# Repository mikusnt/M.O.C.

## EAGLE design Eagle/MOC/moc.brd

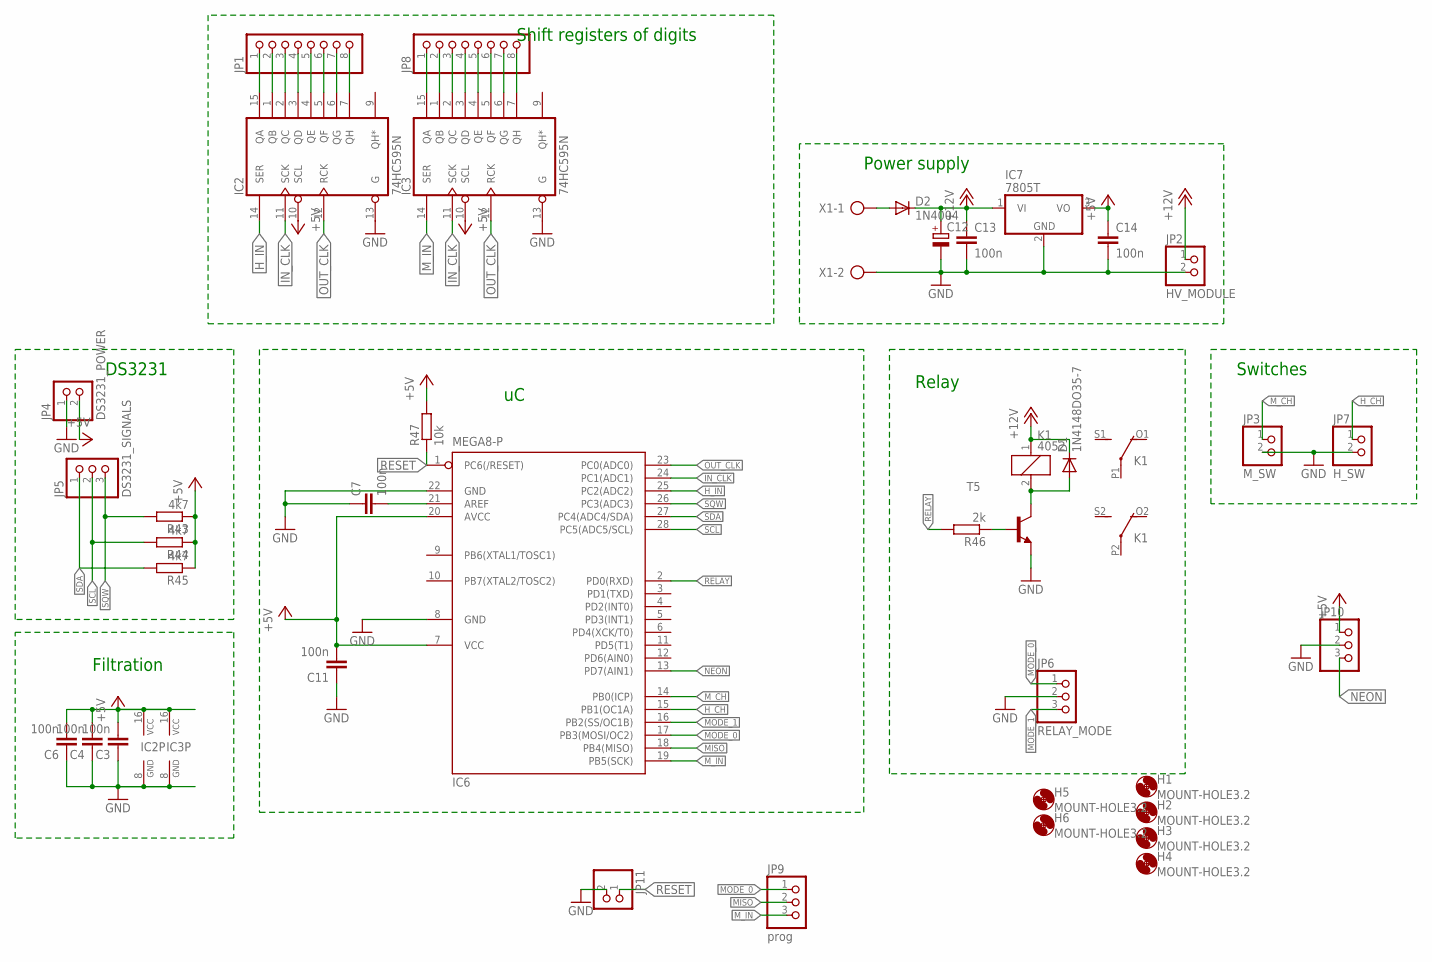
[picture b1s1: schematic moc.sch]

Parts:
C3, C4, C6, C7, C11, C13, C14: 100n; C025-025X050
C12: CPOL-EUE3.5-8; E3,5-8
D1: 1N4148DO35-7; DO35-7
D2: 1N4004; DO41-10
H1, H2, H3, H4, H5, H6: MOUNT-HOLE3.2; 3,2
IC2, IC3: 74HC595N; DIL16
IC6: MEGA8-P; DIL28-3
IC7: 7805T; TO220H
JP1, JP8: PINHD-1X8; 1X08
JP2: HV_MODULE; 1X02
JP3: M_SW; 1X02
JP4: DS3231_POWER; 1X02
JP5: DS3231_SIGNALS; 1X03
JP6: RELAY_MODE; 1X03
JP7: H_SW; 1X02
JP9: prog; 1X03
JP10: PINHD-1X3; 1X03
JP11: PINHD-1X2/90; 1X02/90
K1: 4052; F4052
R43, R44, R45: 4k7; 0207/10
R46: 2k; 0207/7
R47: 10k; 0207/10
T5: BC337-16-NPN-TO92-CBE; TO92-CBE
X1: AK300/2

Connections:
+5V: C3.2, C4.2, C6.2, C11.2, C14.1, IC2.10 (SCL), IC2.16 (VCC), IC3.10 (SCL), IC3.16 (VCC), IC6.7 (VCC), IC6.20 (AVCC), IC7.3 (VO), JP4.2, JP10.1, R43.1, R44.1, R45.1, R47.2
+12V: C12.+, C13.1, D1.C, D2.C, IC7.1 (VI), JP2.1, K1.1
D8: IC3.7 (QH), JP8.8
D9: IC3.6 (QG), JP8.7
D10: IC3.5 (QF), JP8.6
D11: IC3.4 (QE), JP8.5
D12: IC3.3 (QD), JP8.4
D13: IC3.2 (QC), JP8.3
D14: IC3.1 (QB), JP8.2
D15: IC3.15 (QA), JP8.1
D16: IC2.7 (QH), JP1.8
D17: IC2.6 (QG), JP1.7
D18: IC2.5 (QF), JP1.6
D19: IC2.4 (QE), JP1.5
D20: IC2.3 (QD), JP1.4
D21: IC2.2 (QC), JP1.3
D22: IC2.1 (QB), JP1.2
D23: IC2.15 (QA), JP1.1
GND: C3.1, C4.1, C6.1, C7.1, C11.1, C12.-, C13.2, C14.2, IC2.8 (GND), IC2.13 (G), IC3.8 (GND), IC3.13 (G), IC6.8 (GND), IC6.22 (GND), IC7.2 (GND), JP2.2, JP3.2, JP4.1, JP6.2, JP7.2, JP10.2, JP11.2, T5.E, X1.2
H_CH: IC6.15 (PB1(OC1A)), JP7.1
H_IN: IC2.14 (SER), IC6.25 (PC2(ADC2))
IN_CLK: IC2.11 (SCK), IC3.11 (SCK), IC6.24 (PC1(ADC1))
MISO: IC6.18 (PB4(MISO)), JP9.2
MODE_0: IC6.17 (PB3(MOSI/OC2)), JP6.1, JP9.1
MODE_1: IC6.16 (PB2(SS/OC1B)), JP6.3
M_CH: IC6.14 (PB0(ICP)), JP3.1
M_IN: IC3.14 (SER), IC6.19 (PB5(SCK)), JP9.3
unnamed: D2.A, X1.1
unnamed: C7.2, IC6.21 (AREF)
unnamed: D1.A, K1.2, T5.C
unnamed: R46.1, T5.B
NEON: IC6.13 (PD7(AIN1)), JP10.3
OUT_CLK: IC2.12 (RCK), IC3.12 (RCK), IC6.23 (PC0(ADC0))
RELAY: IC6.2 (PD0(RXD)), R46.2
RESET: IC6.1 (PC6(/RESET)), JP11.1, R47.1
SCL: IC6.28 (PC5(ADC5/SCL)), JP5.2, R44.2
SDA: IC6.27 (PC4(ADC4/SDA)), JP5.1, R45.2
SQW: IC6.26 (PC3(ADC3)), JP5.3, R43.2

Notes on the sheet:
DS3231
Relay
Power supply
Filtration
Shift registers of digits
Switches

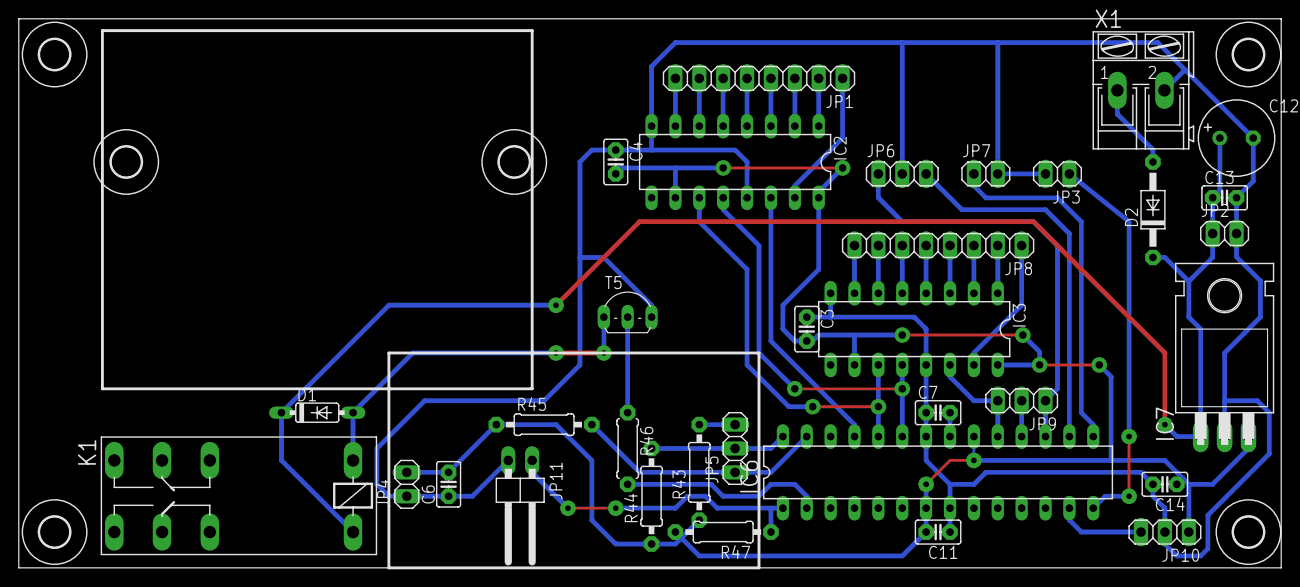
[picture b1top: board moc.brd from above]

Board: 2 copper layers, 134.3 x 58.4 mm, 39 parts (0 on the bottom side), 38 nets.

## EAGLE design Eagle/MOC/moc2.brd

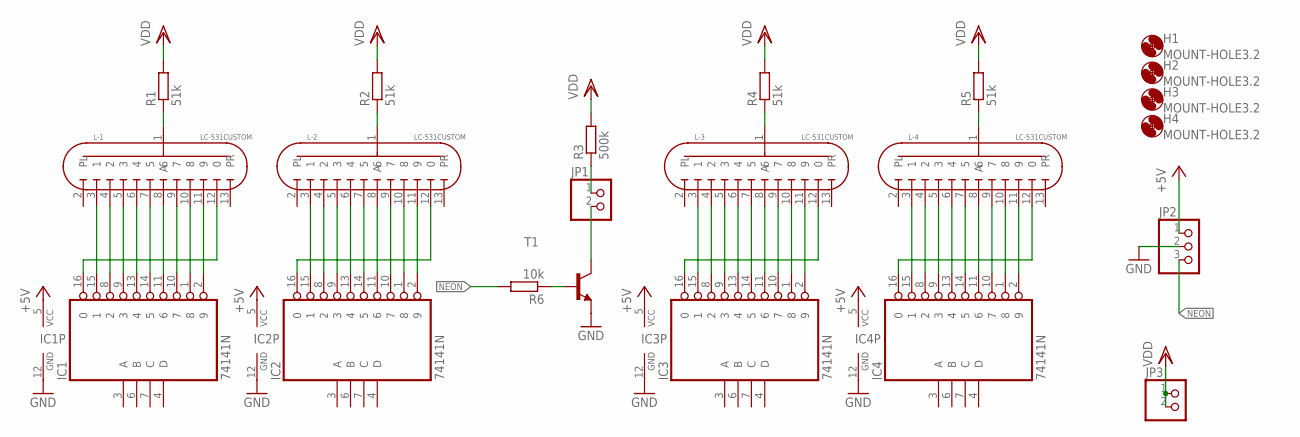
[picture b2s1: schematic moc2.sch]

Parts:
H1, H2, H3, H4: MOUNT-HOLE3.2; 3,2
IC1, IC2, IC3, IC4: 74141N; DIL16
JP1: PINHD-1X2; 1X02
JP2: PINHD-1X3/90; 1X03/90
JP3: PINHD-1X2/90; 1X02/90
L-1, L-2, L-3, L-4: LC-531CUSTOM; LC-531_PIN_SOCKET
R1, R2, R4, R5: 51k; 0207/10
R3: 500k; 0207/10
R6: 10k; 0207/10
T1: BF422-NPN-TO92-BCE; TO92-BCE

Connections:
+5V: IC1.5 (VCC), IC2.5 (VCC), IC3.5 (VCC), IC4.5 (VCC), JP2.1
GND: IC1.12 (GND), IC2.12 (GND), IC3.12 (GND), IC4.12 (GND), JP2.2, T1.E
unnamed: IC1.15 (1), L-1.3 (1)
unnamed: IC1.8 (2), L-1.4 (2)
unnamed: IC1.9 (3), L-1.5 (3)
unnamed: IC1.13 (4), L-1.6 (4)
unnamed: IC1.14 (5), L-1.7 (5)
unnamed: IC1.11 (6), L-1.8 (6)
unnamed: IC1.10 (7), L-1.9 (7)
unnamed: IC1.1 (8), L-1.10 (8)
unnamed: IC1.2 (9), L-1.11 (9)
unnamed: IC1.16 (0), L-1.12 (0)
unnamed: L-1.1 (A), R1.1
unnamed: IC2.15 (1), L-2.3 (1)
unnamed: IC2.8 (2), L-2.4 (2)
unnamed: IC2.9 (3), L-2.5 (3)
unnamed: IC2.13 (4), L-2.6 (4)
unnamed: IC2.14 (5), L-2.7 (5)
unnamed: IC2.11 (6), L-2.8 (6)
unnamed: IC2.10 (7), L-2.9 (7)
unnamed: IC2.1 (8), L-2.10 (8)
unnamed: IC2.2 (9), L-2.11 (9)
unnamed: IC2.16 (0), L-2.12 (0)
unnamed: L-2.1 (A), R2.1
unnamed: JP1.2, T1.C
unnamed: JP1.1, R3.1
unnamed: IC3.15 (1), L-3.3 (1)
unnamed: IC3.8 (2), L-3.4 (2)
unnamed: IC3.9 (3), L-3.5 (3)
unnamed: IC3.13 (4), L-3.6 (4)
unnamed: IC3.14 (5), L-3.7 (5)
unnamed: IC3.11 (6), L-3.8 (6)
unnamed: IC3.10 (7), L-3.9 (7)
unnamed: IC3.1 (8), L-3.10 (8)
unnamed: IC3.2 (9), L-3.11 (9)
unnamed: IC3.16 (0), L-3.12 (0)
unnamed: L-3.1 (A), R4.1
unnamed: IC4.15 (1), L-4.3 (1)
unnamed: IC4.8 (2), L-4.4 (2)
unnamed: IC4.9 (3), L-4.5 (3)
unnamed: IC4.13 (4), L-4.6 (4)
unnamed: IC4.14 (5), L-4.7 (5)
unnamed: IC4.11 (6), L-4.8 (6)
unnamed: IC4.10 (7), L-4.9 (7)
unnamed: IC4.1 (8), L-4.10 (8)
unnamed: IC4.2 (9), L-4.11 (9)
unnamed: IC4.16 (0), L-4.12 (0)
unnamed: L-4.1 (A), R5.1
unnamed: R6.1, T1.B
NEON: JP2.3, R6.2
VDD: JP3.1, JP3.2, R1.2, R2.2, R3.2, R4.2, R5.2

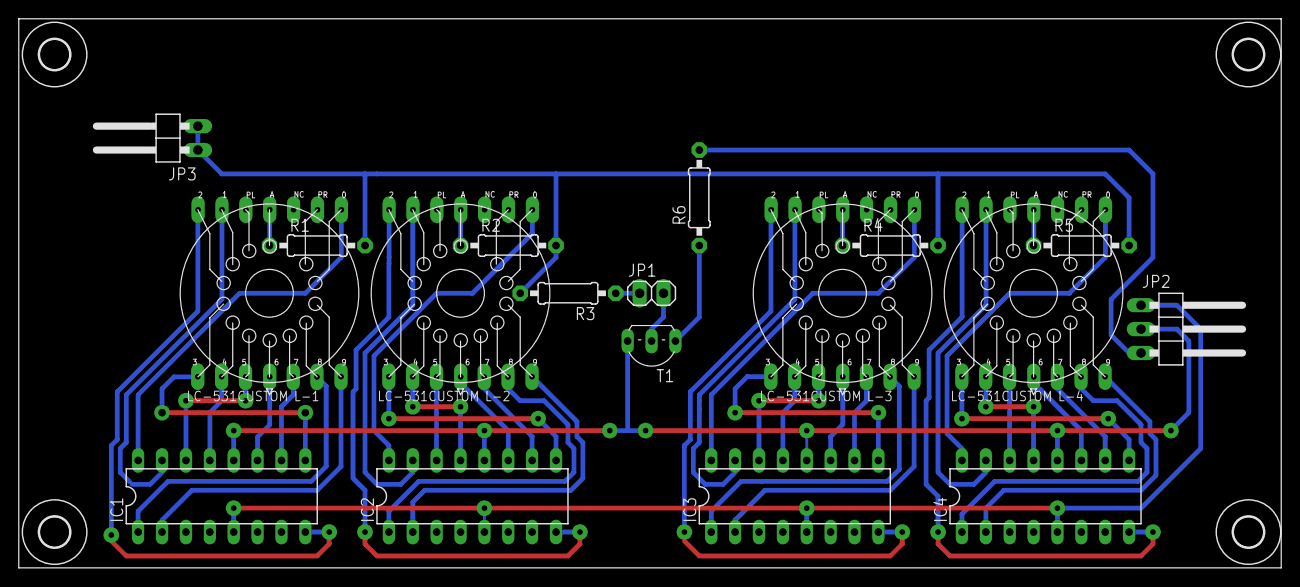
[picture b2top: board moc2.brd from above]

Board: 2 copper layers, 134.3 x 58.4 mm, 22 parts (0 on the bottom side), 51 nets.

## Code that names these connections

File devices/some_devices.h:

/*!
 * @file some_devices.h
 * @author 		Mikolaj Stankowiak <br>
 * 				mik-stan@go2.pl
 * $Modified: 2019-03-03 $
 * $Created: 2017-11-04 $
 * @version 1.0
 * From Matrix Clock project.
 *
 * Used uC pins: 5<br>
 * Header file containing configuration of timers, rename time and relay mode buttons.
 */

#ifndef SOME_DEVICES_H_
#define SOME_DEVICES_H_

#include "../group_includes.h"

/*
 *
 *		Macros
 *
 */
// SQW
//! direction register of square wave second signal from DS3231
#define SQW_DDR DDRC
//! state register of square wave second signal from DS3231
#define SQW_PORT PORTC
//! value register of square wave second signal from DS3231
#define SQW_PIN PINC
//! address register of square wave second signal from DS3231
#define SQW_ADDR (1 << PC3)
//! check state of square wave second signal from DS3231
#define SQW_IS_HIGH() (SQW_PIN & SQW_ADDR)

// Hour
//! direction register of hour button
#define HOUR_DDR DDRB
//! state register of hour button
#define HOUR_PORT PORTB
//! value register of hour button
#define HOUR_PIN PINB
//! address register of hour button
#define HOUR_ADDR (1 << PB1)
//! check state of hour button
#define HOUR_IS_ON() (!(HOUR_PIN & HOUR_ADDR))

// Minute
//! direction register of minute button
#define MINUTE_DDR DDRB
//! state register of minute button
#define MINUTE_PORT PORTB
//! value register of minute button
#define MINUTE_PIN PINB
//! address register of minute button
#define MINUTE_ADDR (1 << PB0)
//! check state of minute button
#define MINUTE_IS_ON() (!(MINUTE_PIN & MINUTE_ADDR))

// Relay mode
//! direction register of relay mode button
#define RM_DDR DDRB
//! state register of relay mode button
#define RM_PORT PORTB
//! value register of relay mode button
#define RM_PIN PINB
//! address register of relay mode button
// Choose between single and double mode
//#define RM_ADDR ((1 << PB2) | (1 << PB3))
#define RM_ADDR (1 << PB3)
//! check state of relay mode button
//#define RELAY_MODE() ((~((RM_PIN & RM_ADDR) >> 2)) & 0x03)
#define RELAY_MODE() ((~((RM_PIN & RM_ADDR) >> 3)) & 0x01)

//! direction register of neon between hours and minutes lamps
#define NEON_DDR DDRD
//! state register of neon between hours and minutes lamps
#define NEON_PORT PORTD
//! address of neon between hours and minutes lamps
#define NEON_ADDR (1 << PD7)
//! set neon state to high
#define NEON_ON() NEON_PORT |= NEON_ADDR
//! set neon state to low
#define NEON_OFF() NEON_PORT &= ~NEON_ADDR

/*
 *
 *		Declaration of functions
 *
 */

//! Initialize buttons containing hour, minute and relay mode buttons
extern void ButtonsInit();
//! Initialize Timer2 to cunting time between DS3231 interrupts
extern void Timer2Init();
//! Initialize PCINT interrupt
extern void PCINTInit();
//! Initialize reisters of neon
extern void NeonInit();
//! Power reduction
extern void PowerReduction();
//! rename state of point
inline void NeonRename();
//! simple blinking test of neon
extern void NeonTest();
//! rename neon state
inline void NeonRename() {
	NEON_PORT ^= NEON_ADDR;
}

#endif /* SOME_DEVICES_H_ */

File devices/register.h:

/*!
 * @file register.h
 * @author 		Mikolaj Stankowiak <br>
 * 				mik-stan@go2.pl
 * $Modified: 2019-03-03 $
 * $Created: 2017-11-04 $
 * @version 1.2
 * From Matrix Clock project.
 *
 * Used uC pins: 4<br>
 * Features:<br>
 * -...
 * -...
 */

#ifndef register_H_
#define register_H_

#include "../group_includes.h"
#include "ds3231.h"


// HINT optional seconds register
#define WITH_SECONDS 0

/*
 *		optional third, WITH_SECONDS: hours, NORMAL: -
 */
//! direction register of hour serial data input
#define THIRD_DATA_DDR DDRD
//! state register of hour serial data input
#define THIRD_DATA_PORT PORTD
//! address of hour serial data input
#define THIRD_DATA_ADDR (1 << PD1)
//! set high state to hour serial data input
#define THIRD_DATA_HIGH() THIRD_DATA_PORT |= THIRD_DATA_ADDR
//! set low state to hour serial data input
#define THIRD_DATA_LOW() THIRD_DATA_PORT &= ~THIRD_DATA_ADDR


/*
 *		second,WITH_SECONDS: minutes, NORMAL: hours
 */
//! direction register of minute serial data input
#define SECOND_DATA_DDR DDRC
//! state register of minute serial data input
#define SECOND_DATA_PORT PORTC
//! address of minute serial data input
#define SECOND_DATA_ADDR (1 << PC2)
//! set high state to minute serial data input
#define SECOND_DATA_HIGH() SECOND_DATA_PORT |= SECOND_DATA_ADDR
//! set low state to minute serial data input
#define SECOND_DATA_LOW() SECOND_DATA_PORT &= ~SECOND_DATA_ADDR


/*
 * 		first, WITH_SECONDS: seconds, NORMAL: minutes
 */
//! direction register of second serial data input
#define FIRST_DATA_DDR DDRB
//! state register of second serial data input
#define FIRST_DATA_PORT PORTB
//! address of second serial data input
#define FIRST_DATA_ADDR (1 << PB5)
//! set high state to second serial data input
#define FIRST_DATA_HIGH() FIRST_DATA_PORT |= FIRST_DATA_ADDR
//! set low state to second serial data input
#define FIRST_DATA_LOW() FIRST_DATA_PORT &= ~FIRST_DATA_ADDR


//! direction register of clk of time data input
#define TIME_CLK_DATA_DDR DDRC
//! state register of clk of time data input
#define TIME_CLK_DATA_PORT PORTC
//! address of clk of time data input
#define TIME_CLK_DATA_ADDR (1 << PC1)
/*

		Y_RESET, not used
//! direction register of reset Y register
#define Y_RESET_DDR DDRD
//! state register of reset Y register
#define Y_RESET_PORT PORTD
//! address of reset Y register
#define Y_RESET_ADDR (1 << PD3)
//! set ON Y register
#define Y_ON() Y_RESET_PORT &= ~Y_RESET_ADDR
//! set OFF Y register
#define Y_OFF() Y_RESET_PORT |= Y_RESET_ADDR*/

/*
 *		LATCH
 */
//! direction register of parallel output enable of all registers
#define LATCH_DDR DDRC
//! state register of parallel output enable of all registers
#define LATCH_PORT PORTC
//! address of parallel output enable of all registers
#define LATCH_ADDR (1 << PC0)
//! set high state of parallel output enable of all registers
#define LATCH_HIGH() LATCH_PORT |= LATCH_ADDR
//! set low state of parallel output enable of all registers
#define LATCH_LOW() LATCH_PORT &= ~LATCH_ADDR


/*
 *
 *		Declaration of functions
 *
 */
//! initialize registers
extern void RegistersInit();
//! send byte table to time registers
inline void SendRegistersTime(uint8_t uiHour, uint8_t uiMinute,
		uint8_t uiSecond, bool bWithLoad);
//! send zeros to time registers
inline void ClearRegistersTime(bool bWithLoad);
//! simple test, send all digits to hour and minute registers
void RegistersTest(bool bForeverLoop);

/*
 *
 * 		Definitions of inline functions
 *
 */

//! to load new bytes to X registers
inline void Time_CLK_01() {
	TIME_CLK_DATA_PORT &= ~TIME_CLK_DATA_ADDR;
	TIME_CLK_DATA_PORT |= TIME_CLK_DATA_ADDR;

}

//! to reload parallel output in all registers
inline void LATCH_01() {
	LATCH_LOW();
	LATCH_HIGH();
}

/*! @param		uiHour value of hour lamps
 *  @param		uiMinute value of minute lamps
 *  @param		uiSecond value of second lamps
 *  @param		bWithLoad enable to reload parallel output*/
inline void SendRegistersTime(uint8_t uiHour, uint8_t uiMinute, uint8_t uiSecond, bool bWithLoad) {
	register int8_t i;
	register uint8_t uiHourBCD = dec2bcdrev(uiHour);
	register uint8_t uiMinuteBCD = dec2bcdrev(uiMinute);
	register uint8_t uiSecondBCD = dec2bcdrev(uiSecond);
	//register uint8_t uiSecondBCD = dec2bcd(uiSecond);
	for (i = 0; i < 8; i++) {
		if (uiHourBCD % 2) {
			if (WITH_SECONDS)
				THIRD_DATA_HIGH();
			else
				SECOND_DATA_HIGH();
		} else {
			if (WITH_SECONDS)
				THIRD_DATA_LOW();
			else
				SECOND_DATA_LOW();
		}

		if (uiMinuteBCD % 2) {
			if (WITH_SECONDS)
				SECOND_DATA_HIGH();
			else
				FIRST_DATA_HIGH();
		} else {
			if (WITH_SECONDS)
				SECOND_DATA_LOW();
			else
				FIRST_DATA_LOW();

		}

		if (WITH_SECONDS) {
			if (uiSecondBCD % 2) THIRD_DATA_HIGH();
				else THIRD_DATA_LOW();
		}
		//if (uiSecondBCD) S_DATA_HIGH();
		//	else S_DATA_LOW();
		Time_CLK_01();
		uiHourBCD >>= 1;
		uiMinuteBCD >>= 1;
		uiSecondBCD >>= 1;
		//uiSecondBCD = uiSecondBCD >> 1;
	}
	if (bWithLoad) LATCH_01();
} // END inline void SendRegistersTime

/*! @param		bWithLoad enable to reload parallel output*/
inline void ClearRegistersTime(bool bWithLoad) {
	register uint8_t i;
	THIRD_DATA_LOW();
	SECOND_DATA_LOW();
	//S_DATA_LOW();
	for (i = 0; i < 8; i++) {
		Time_CLK_01();
	}
	if (bWithLoad) LATCH_01();
} // END inline void SendRegistersX

#endif /* 54HC595_H_ */

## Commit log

2018-11-17 simple mainboard schematic
2018-11-18 main project cstructure
2018-12-07 time registers
2018-12-07 switches
2019-03-02 relay in main file, code of tests
2019-03-03 hardware tests, all features
2019-04-15 cathodes heat on mode, relay parameters
2019-05-01 decrease frequency to 1 MHz
2019-06-20 optional seconds register
2019-08-13 universal second register switch
2019-08-13 1MHz freq and two modes of relay mode buttons
2021-01-07 only one mode of relay, lamp diagnostic mode by press two buttons
